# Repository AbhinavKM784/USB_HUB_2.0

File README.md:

# USB 4 port 2.0 Hub

A custom-designed 4-port USB 2.0 hub built around the GL850G USB Hub Controller.

## Overview

This USB hub features:

- 1 × USB C upstream port
- 2 × USB Type-A downstream ports
- 2 × USB Type-C downstream ports
- USB 2.0 High-Speed support (up to 480 Mbps)
- Plug-and-play operation

## Specifications

- Hub Controller - GL850G 
- USB Standard - USB 2.0
- Maximum Speed - 480 Mbps
- Upstream Ports - 1 
- USB-A Ports - 2 
- USB-C Ports - 2 

## Bill of Materials (BOM)

|  # | Component        | Value / Part                         | Qty |   Price (INR) |   Price (USD) |
| -: | ---------------- | ------------------------------------ | --: | ------------: | ------------: |
|  1 | PCB              | Fabricated by LionCircuits           |   1 |     ₹1,012.00 |       $10.626 |
|  2 | Capacitor        | 10 µF                                |   2 |        ₹21.60 |       $0.2268 |
|  3 | Capacitor        | 1 µF                                 |   4 |        ₹21.10 |      $0.22155 |
|  4 | Capacitor        | 22 pF                                |   2 |        ₹20.00 |        $0.210 |
|  5 | Capacitor        | 100 nF                               |   5 |        ₹19.00 |       $0.1995 |
|  6 | USB IC           | GL850G                               |   1 |        ₹84.00 |        $0.882 |
|  7 | USB-C Receptacle | USB 2.0, 16P                         |   3 |        ₹71.00 |       $0.7455 |
|  8 | USB-A Receptacle | Molex 67643                          |   2 |        ₹15.00 |       $0.1575 |
|  9 | Resistor         | 5.1 kΩ                               |   6 |        ₹11.00 |       $0.1155 |
| 10 | Resistor         | 680 Ω                                |   1 |        ₹13.00 |       $0.1365 |
| 11 | Resistor         | 10 kΩ                                |   1 |        ₹11.00 |       $0.1155 |
| 12 | Crystal          | 12 MHz                               |   1 |        ₹24.00 |        $0.252 |
| 13 | Soldering Wire   | 40/60, 0.8 mm                        |   1 |        ₹53.00 |       $0.5565 |
| 14 | Magnets          | 3 mm Diameter × 3 mm Thick Neodymium |   8 |        ₹76.00 |        $0.798 |
| 15 | M2 Screws        | M2 × 8 mm Phillips CSK SS 304        |   5 |         ₹8.00 |        $0.084 |
| 16 | M2 Brass Inserts | M2 × 6 mm Brass Threaded Inserts     |   5 |        ₹12.00 |        $0.126 |
|    | **Total**        |                                      |     | **₹1,471.70** | **$15.45285** |

### Additional Hardware

* **8 × 3 mm × 3 mm neodymium magnets** — used for the enclosure's magnetic closure.
* **5 × M2 × 8 mm Phillips countersunk screws** — used for PCB mounting.
* **5 × M2 × 6 mm brass threaded inserts** — used as threaded mounting points for the PCB screws.

### Component Links

* [PCB — LionCircuits](https://www.lioncircuits.com/)
* [10 µF Capacitor — KTRON](https://www.ktron.in/product/10uf-25v-ceramic-capacitor-smd-0805/)
* [1 µF Capacitor — Robu](https://robu.in/product/gcm21br71e105ka56k-murata-electronics-25v-1uf-x7r-%c2%b110-0805-multilayer-ceramic-capacitor/)
* [22 pF Capacitor — KTRON](https://www.ktron.in/product/22pf-100v-multi-layered-ceramic-capacitor/)
* [100 nF Capacitor — KTRON](https://www.ktron.in/product/100nf-100v-ceramic-capacitor-0805/)
* [GL850G USB IC — Hubtronics](https://hubtronics.in/1884)
* [USB-C Receptacle — KTRON](https://www.ktron.in/product/mup-u20401-03-usb-type-c-16-pin-smd-connector/)
* [USB-A Receptacle — KTRON](https://www.ktron.in/product/usb-type-a-female-connector/)
* [5.1 kΩ Resistor — Robu](https://robu.in/product/erj6geyj512v-panasonic-125mw-thick-film-resistors/)
* [680 Ω Resistor — Robu](https://robu.in/product/rt0805fr-07680rl-yageo-125mw-thick-film-resistor/)
* [10 kΩ Resistor — Robu](https://robu.in/product/ac0805jr-0710kl-yageo-res-thick-film-0805-10k-ohm/)
* [12 MHz Crystal — KTRON](https://www.ktron.in/product/12-mhz-crystal-smd-hc49smd-xyc/)
* [Soldering Wire — Robu](https://robu.in/product/tin-wire-soldering-tubeus-0-8mm-40-60/)
* [3 mm × 3 mm Neodymium Magnets — OnlyScrews](https://onlyscrews.in/products/3mm-x-3mm-neodymium-disc-magnets-n35-dia-3mm-thickness-3mm)
* [M2 × 8 mm Phillips CSK Screws — OnlyScrews](https://onlyscrews.in/products/m2-x-8mm-phillips-csk-ss-304-screw-dia-2mm-length-8mm)
* [M2 × 6 mm Brass Threaded Inserts — OnlyScrews](https://onlyscrews.in/products/m2-x-6mm-brass-threaded-inserts)

### Shipping

| Supplier           | Shipping (INR) | Shipping (USD) |
| ------------------ | -------------: | -------------: |
| Hubtronics         |         ₹75.00 |         $0.788 |
| Robu               |         ₹50.00 |         $0.525 |
| Ktron              |         ₹77.00 |         $0.809 |
| Onlyscrews         |         ₹59.00 |         0.7245 |

| **Shipping Total** |    **₹272.00** |     **2.8455** |

### Total Cost

|                 |           INR |         USD |
| --------------- | ------------: | ----------: |
| Components      |     ₹1,375.70 |     $14.445 |
| Shipping        |       ₹202.00 |      $2.121 |
| **Grand Total** | **₹1,742.70** | **$18.299** |

> **Note:** Prices are approximate and may change depending on supplier pricing and availability.

## Schematic

*Complete circuit schematic of the USB hub.*

## PCB Design

## 3D Model

## CAD Photos And Videos
Bottom Case

<video src="https://github.com/user-attachments/assets/de1a6d5d-6dac-484f-9280-b4399e31e206" controls width="800"></video>

Top Case

<video src="https://github.com/user-attachments/assets/451d31d9-74d8-4081-8db9-19cb0036360e" controls width="800"></video>

PCB 

Assembled Case

<video src="https://github.com/user-attachments/assets/695826ae-f8d0-41ed-982d-1c137125c4df" controls width="800"></video>

## Hardware Architecture

```text
          Host PC
              │
              ▼
       USB Upstream Port
              │
              ▼
          GL850G
      USB Hub Controller
        ┌────┴────┐
        │         │
   USB-A Ports  USB-C Ports
      (2x)         (2x)

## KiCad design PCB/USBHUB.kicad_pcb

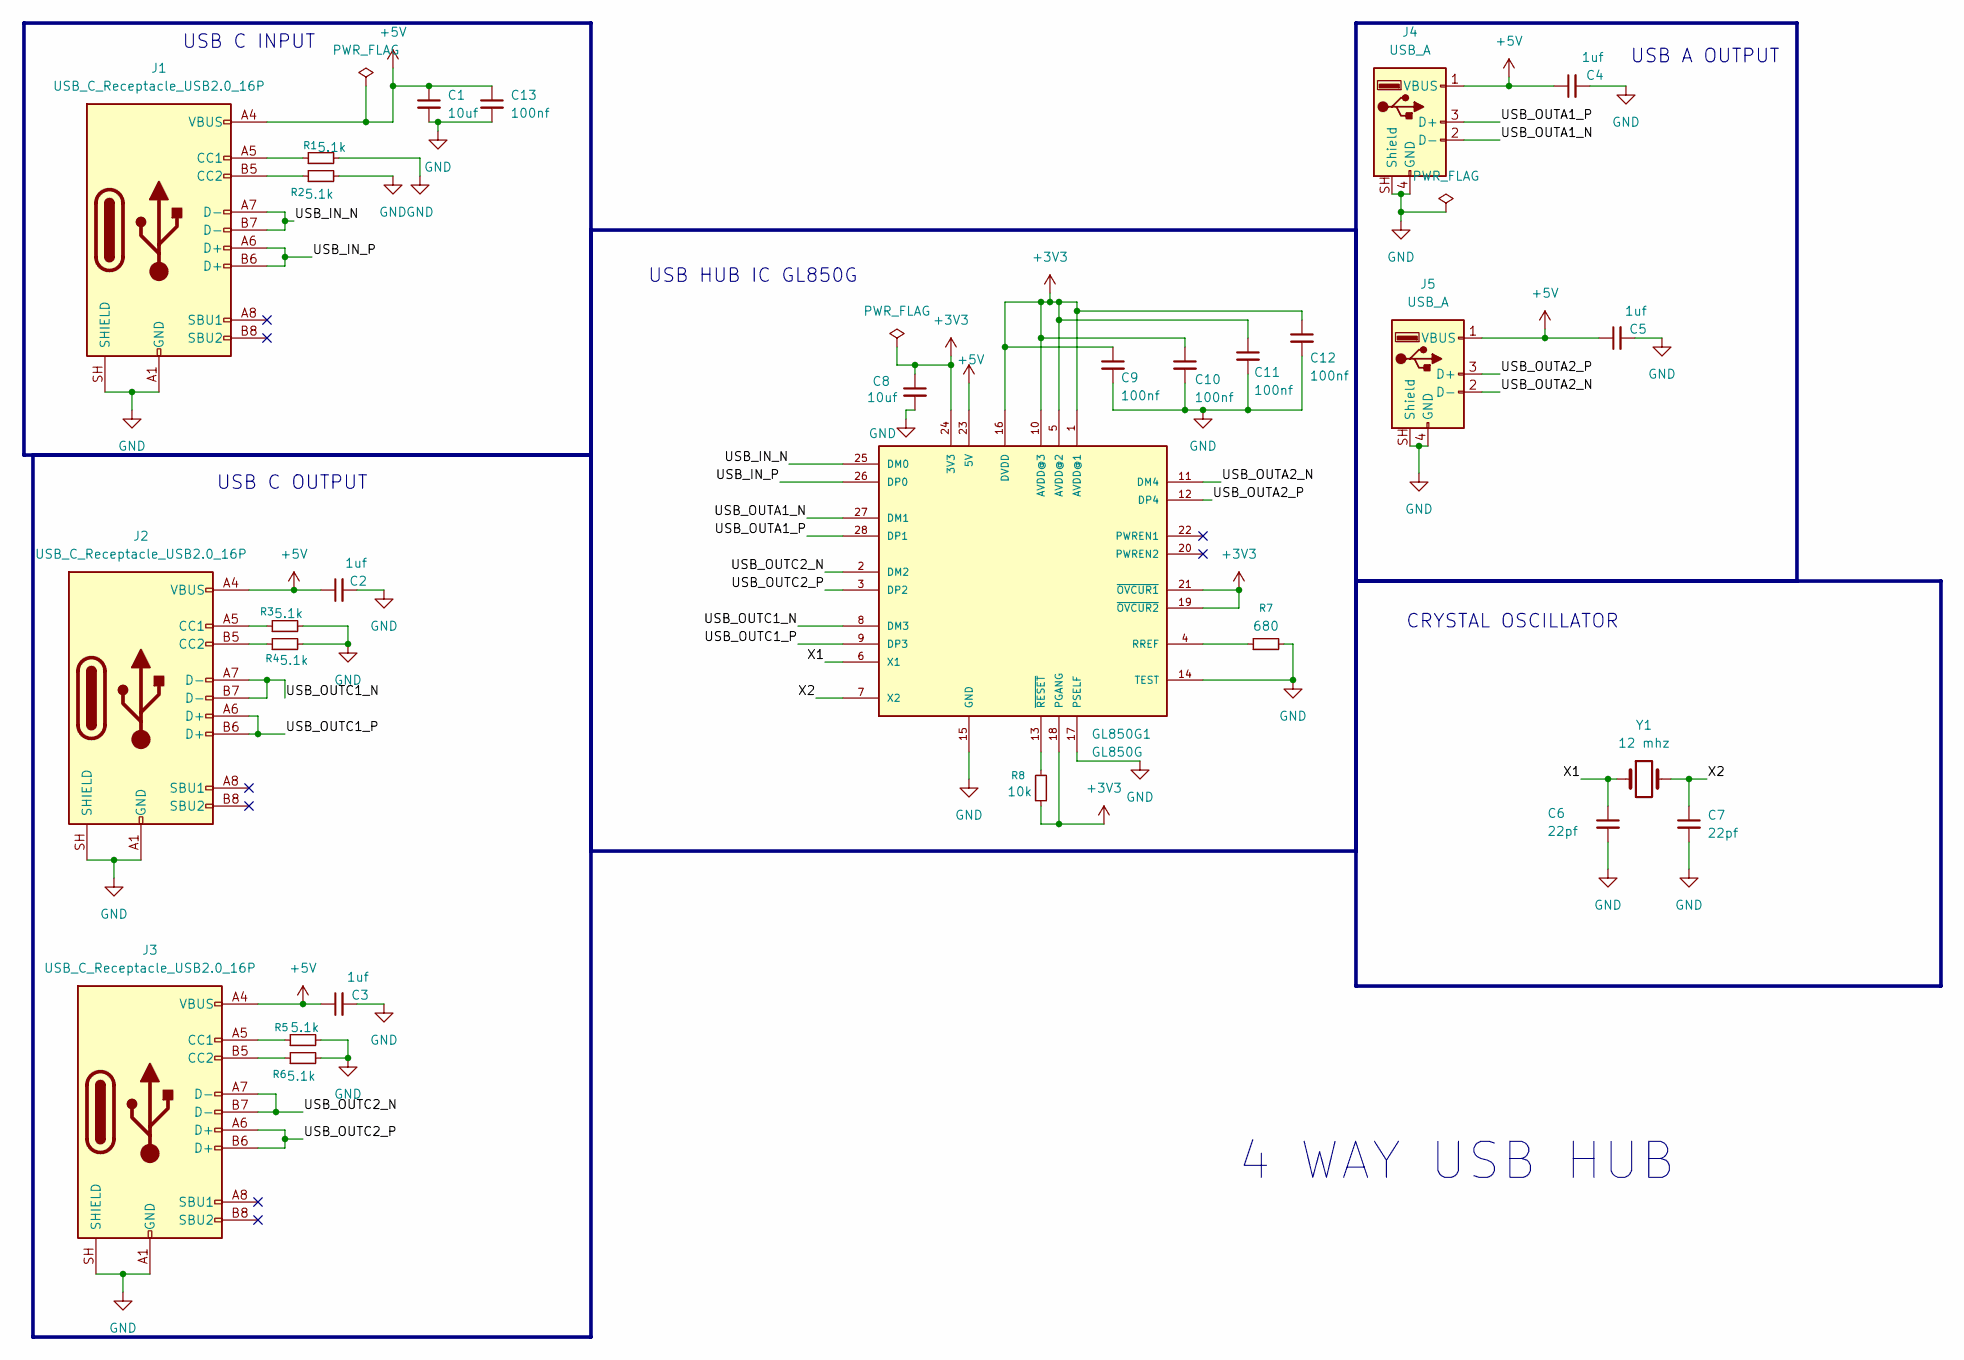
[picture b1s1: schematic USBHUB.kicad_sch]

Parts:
C1, C8: 10uf; C_0805_2012Metric
C2, C3, C4, C5: 1uf; C_0805_2012Metric
C6, C7: 22pf; C_0805_2012Metric
C9, C10, C11, C12, C13: 100nf; C_0805_2012Metric
GL850G1: GL850G; 28SSOP
J1, J2, J3: USB_C_Receptacle_USB2.0_16P; USB_C_Receptacle_HCTL_HC-TYPE-C-16P-01A
J4, J5: USB_A; USB_A_Molex_67643_Horizontal
R1, R2, R3, R4, R5, R6: 5.1k; R_0805_2012Metric
R7: 680; R_0805_2012Metric
R8: 10k; R_0805_2012Metric
Y1: 12 mhz; Crystal_HC49-U_Vertical

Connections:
+3V3: C8.1, C9.1, C10.1, C11.1, C12.1, GL850G1.1 (AVDD@1), GL850G1.5 (AVDD@2), GL850G1.10 (AVDD@3), GL850G1.16 (DVDD), GL850G1.18 (PGANG), GL850G1.19 (~OVCUR2), GL850G1.21 (~OVCUR1), GL850G1.24 (3V3), R8.1
+5V: C1.1, C2.1, C3.1, C4.1, C5.1, C13.1, GL850G1.23 (5V), J1.A4 (VBUS), J1.A9 (VBUS), J1.B4 (VBUS), J1.B9 (VBUS), J2.A4 (VBUS), J2.A9 (VBUS), J2.B4 (VBUS), J2.B9 (VBUS), J3.A4 (VBUS), J3.A9 (VBUS), J3.B4 (VBUS), J3.B9 (VBUS), J4.1 (VBUS), J5.1 (VBUS)
/USB_IN_N: GL850G1.25 (DM0), J1.A7 (D-), J1.B7 (D-)
/USB_IN_P: GL850G1.26 (DP0), J1.A6 (D+), J1.B6 (D+)
/USB_OUTA1_N: GL850G1.27 (DM1), J4.2 (D-)
/USB_OUTA1_P: GL850G1.28 (DP1), J4.3 (D+)
/USB_OUTA2_N: GL850G1.11 (DM4), J5.2 (D-)
/USB_OUTA2_P: GL850G1.12 (DP4), J5.3 (D+)
/USB_OUTC1_N: GL850G1.8 (DM3), J2.A7 (D-), J2.B7 (D-)
/USB_OUTC1_P: GL850G1.9 (DP3), J2.A6 (D+), J2.B6 (D+)
/USB_OUTC2_N: GL850G1.2 (DM2), J3.A7 (D-), J3.B7 (D-)
/USB_OUTC2_P: GL850G1.3 (DP2), J3.A6 (D+), J3.B6 (D+)
/X1: C6.1, GL850G1.6 (X1), Y1.1
/X2: C7.1, GL850G1.7 (X2), Y1.2
GND: C1.2, C2.2, C3.2, C4.2, C5.2, C6.2, C7.2, C8.2, C9.2, C10.2, C11.2, C12.2, C13.2, GL850G1.14 (TEST), GL850G1.15 (GND), GL850G1.17 (PSELF), J1.A1 (GND), J1.A12 (GND), J1.B1 (GND), J1.B12 (GND), J1.SH (SHIELD), J2.A1 (GND), J2.A12 (GND), J2.B1 (GND), J2.B12 (GND), J2.SH (SHIELD), J3.A1 (GND), J3.A12 (GND), J3.B1 (GND), J3.B12 (GND), J3.SH (SHIELD), J4.4 (GND), J4.SH (Shield), J5.4 (GND), J5.SH (Shield), R1.2, R2.2, R3.2, R4.2, R5.2, R6.2, R7.2
unnamed: GL850G1.4 (RREF), R7.1
unnamed: GL850G1.13 (~RESET), R8.2
unnamed: J1.A5 (CC1), R1.1
unnamed: J1.B5 (CC2), R2.1
unnamed: J2.A5 (CC1), R3.1
unnamed: J2.B5 (CC2), R4.1
unnamed: J3.A5 (CC1), R5.1
unnamed: J3.B5 (CC2), R6.1

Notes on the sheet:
USB HUB IC GL850G
CRYSTAL OSCILLATOR
4 WAY USB HUB
USB C OUTPUT
USB A OUTPUT
USB C INPUT

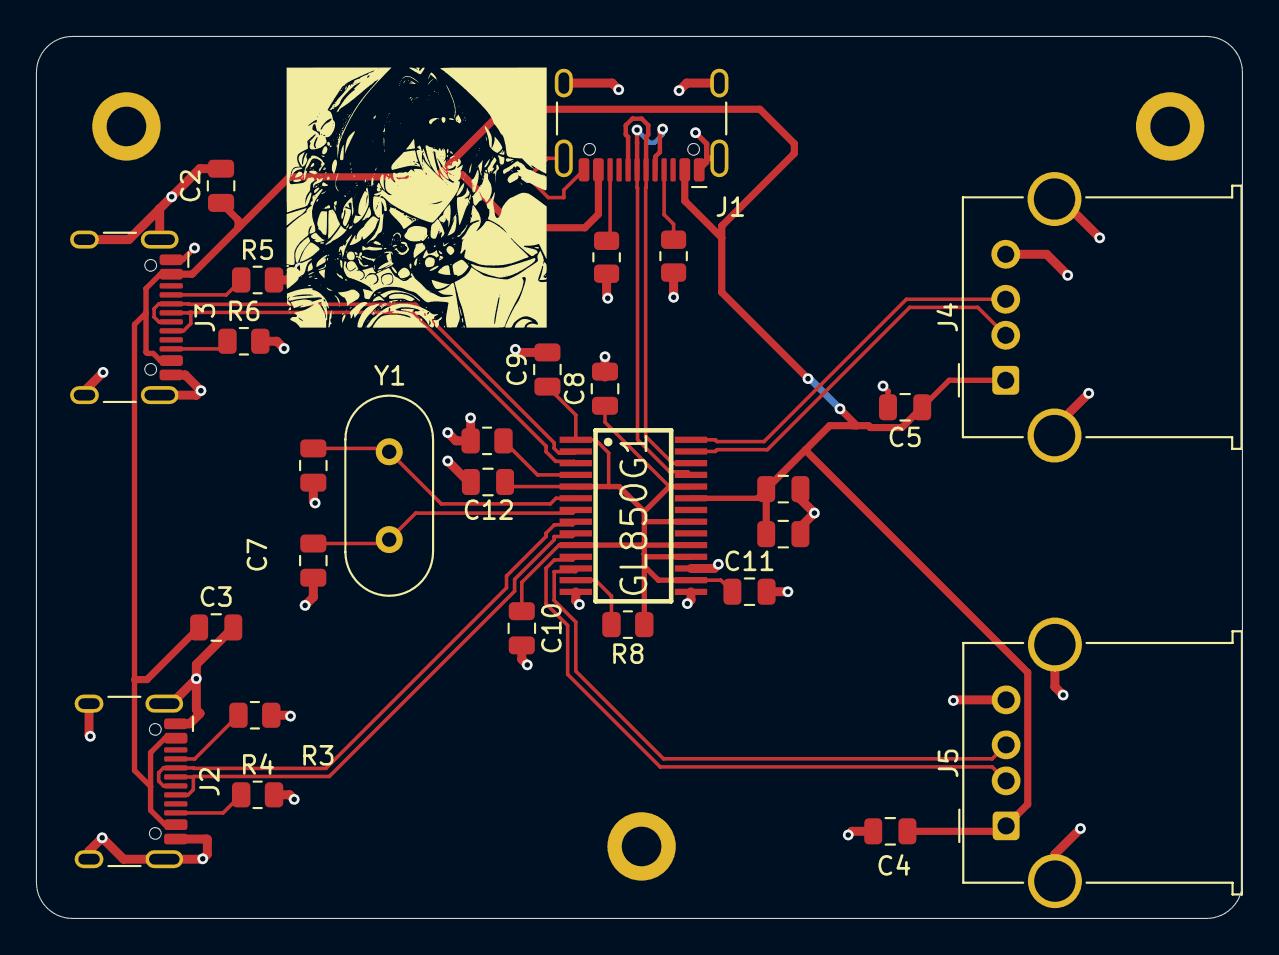
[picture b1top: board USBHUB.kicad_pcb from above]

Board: 2 copper layers, 67.0 x 49.0 mm, 28 parts (0 on the bottom side), 23 nets.

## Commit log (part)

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2026-06-11 Create PCB Folder
2026-06-11 Create folder
2026-06-11 FULL README UPDATE
    Expanded the README to include detailed specifications, schematic, PCB design, and 3D model visualizations for the USB 2.0 hub.
